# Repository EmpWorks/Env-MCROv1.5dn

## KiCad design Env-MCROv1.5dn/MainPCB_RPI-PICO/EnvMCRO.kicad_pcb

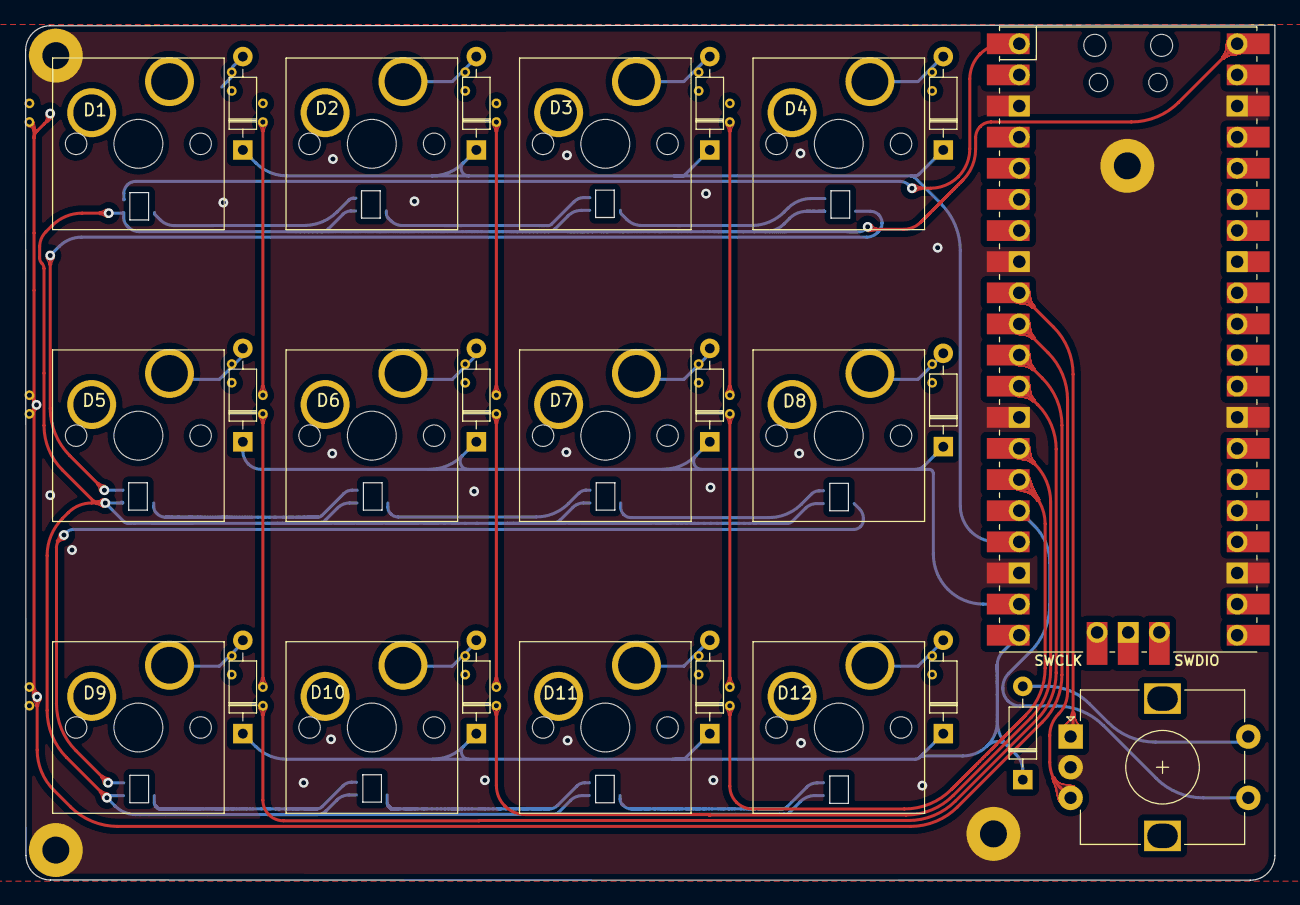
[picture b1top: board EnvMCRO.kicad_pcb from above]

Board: 2 copper layers, 101.9 x 69.8 mm, 43 parts (0 on the bottom side), 37 nets.

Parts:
D1, D2, D3, D4, D5, D6, D7, D8, D9, D10, D11, D12: WS2812B; LED_WS2812B-5050_PLCC4_5.0x5.0mm_P3.2mm
D_0, D_1, D_2, D_3, D_4, D_5, D_6, D_7, D_8, D_9, D_10, D_11, D_14: D; D_DO-35_SOD27_P7.62mm_Horizontal
H1, H2, H3, H4: MountingHole; MountingHole_2.2mm_M2_Pad
K_0, K_1, K_2, K_3, K_4, K_5, K_6, K_7, K_8, K_9, K_10, K_11: KEYSW; MXOnly-1U-Hotswap-Antishear
SW1: Rotary_Encoder_Switch; RotaryEncoder_Alps_EC12E-Switch_Vertical_H20mm
U1: Pico; RPi_Pico_SMD_TH

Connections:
GND: D1.3 (VSS), D2.3 (VSS), D3.3 (VSS), D4.3 (VSS), D5.3 (VSS), D6.3 (VSS), D7.3 (VSS), D8.3 (VSS), D9.3 (VSS), D10.3 (VSS), D11.3 (VSS), D12.3 (VSS), H1.1, H2.1, H3.1, H4.1, SW1.C, U1.3 (GND), U1.8 (GND), U1.13 (GND), U1.18 (GND), U1.23 (GND), U1.28 (GND), U1.38 (GND)
LEDDINPIN: D1.4 (DIN), U1.1 (GPIO0)
unnamed: D1.2 (DOUT), D2.4 (DIN)
unnamed: D2.2 (DOUT), D3.4 (DIN)
unnamed: D3.2 (DOUT), D4.4 (DIN)
unnamed: D4.2 (DOUT), D5.4 (DIN)
unnamed: D5.2 (DOUT), D6.4 (DIN)
unnamed: D6.2 (DOUT), D7.4 (DIN)
unnamed: D7.2 (DOUT), D8.4 (DIN)
unnamed: D8.2 (DOUT), D9.4 (DIN)
unnamed: D10.2 (DOUT), D11.4 (DIN)
unnamed: D9.2 (DOUT), D10.4 (DIN)
unnamed: D11.2 (DOUT), D12.4 (DIN)
unnamed: D_0.2 (A), K_0.2 (ROW)
unnamed: D_1.2 (A), K_1.2 (ROW)
unnamed: D_2.2 (A), K_2.2 (ROW)
unnamed: D_3.2 (A), K_3.2 (ROW)
unnamed: D_4.2 (A), K_4.2 (ROW)
unnamed: D_5.2 (A), K_5.2 (ROW)
unnamed: D_6.2 (A), K_6.2 (ROW)
unnamed: D_7.2 (A), K_7.2 (ROW)
unnamed: D_8.2 (A), K_8.2 (ROW)
unnamed: D_9.2 (A), K_9.2 (ROW)
unnamed: D_10.2 (A), K_10.2 (ROW)
unnamed: D_11.2 (A), K_11.2 (ROW)
unnamed: D_14.2 (A), SW1.S1
ROTA: SW1.B, U1.10 (GPIO7)
ROTB: SW1.A, U1.9 (GPIO6)
VBUS: D1.1 (VDD), D2.1 (VDD), D3.1 (VDD), D4.1 (VDD), D5.1 (VDD), D6.1 (VDD), D7.1 (VDD), D8.1 (VDD), D9.1 (VDD), D10.1 (VDD), D11.1 (VDD), D12.1 (VDD), U1.40 (VBUS)
col0: K_0.1 (COL), K_4.1 (COL), K_8.1 (COL), U1.11 (GPIO8)
col1: K_1.1 (COL), K_5.1 (COL), K_9.1 (COL), U1.12 (GPIO9)
col2: K_2.1 (COL), K_6.1 (COL), K_10.1 (COL), U1.14 (GPIO10)
col3: K_3.1 (COL), K_7.1 (COL), K_11.1 (COL), U1.15 (GPIO11)
col4: SW1.S2, U1.16 (GPIO12)
row0: D_0.1 (K), D_1.1 (K), D_2.1 (K), D_3.1 (K), U1.17 (GPIO13)
row1: D_4.1 (K), D_5.1 (K), D_6.1 (K), D_7.1 (K), U1.19 (GPIO14)
row2: D_8.1 (K), D_9.1 (K), D_10.1 (K), D_11.1 (K), D_14.1 (K), U1.20 (GPIO15)

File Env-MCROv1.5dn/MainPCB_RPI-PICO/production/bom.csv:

Designator,Footprint,Quantity,Value,LCSC Part #
K_4,MXOnly-1U-Hotswap-Antishear,1,KEYSW,
D_6,D_DO-35_SOD27_P7.62mm_Horizontal,1,D,
D_0,D_DO-35_SOD27_P7.62mm_Horizontal,1,D,
K_0,MXOnly-1U-Hotswap-Antishear,1,KEYSW,
D_7,D_DO-35_SOD27_P7.62mm_Horizontal,1,D,
H1,MountingHole_2.2mm_M2_Pad,1,MountingHole,
H4,MountingHole_2.2mm_M2_Pad,1,MountingHole,
H3,MountingHole_2.2mm_M2_Pad,1,MountingHole,
H2,MountingHole_2.2mm_M2_Pad,1,MountingHole,
U1,RPi_Pico_SMD_TH,1,Pico,
D1,LED_WS2812B-5050_PLCC4_5.0x5.0mm_P3.2mm,1,WS2812B,
D2,LED_WS2812B-5050_PLCC4_5.0x5.0mm_P3.2mm,1,WS2812B,
D3,LED_WS2812B-5050_PLCC4_5.0x5.0mm_P3.2mm,1,WS2812B,
D4,LED_WS2812B-5050_PLCC4_5.0x5.0mm_P3.2mm,1,WS2812B,
D5,LED_WS2812B-5050_PLCC4_5.0x5.0mm_P3.2mm,1,WS2812B,
D6,LED_WS2812B-5050_PLCC4_5.0x5.0mm_P3.2mm,1,WS2812B,
D7,LED_WS2812B-5050_PLCC4_5.0x5.0mm_P3.2mm,1,WS2812B,
D8,LED_WS2812B-5050_PLCC4_5.0x5.0mm_P3.2mm,1,WS2812B,
D9,LED_WS2812B-5050_PLCC4_5.0x5.0mm_P3.2mm,1,WS2812B,
D10,LED_WS2812B-5050_PLCC4_5.0x5.0mm_P3.2mm,1,WS2812B,
D11,LED_WS2812B-5050_PLCC4_5.0x5.0mm_P3.2mm,1,WS2812B,
D12,LED_WS2812B-5050_PLCC4_5.0x5.0mm_P3.2mm,1,WS2812B,
SW1,RotaryEncoder_Alps_EC12E-Switch_Vertical_H20mm,1,Rotary_Encoder_Switch,
D_14,D_DO-35_SOD27_P7.62mm_Horizontal,1,D,
K_1,MXOnly-1U-Hotswap-Antishear,1,KEYSW,
D_3,D_DO-35_SOD27_P7.62mm_Horizontal,1,D,
D_10,D_DO-35_SOD27_P7.62mm_Horizontal,1,D,
K_5,MXOnly-1U-Hotswap-Antishear,1,KEYSW,
D_4,D_DO-35_SOD27_P7.62mm_Horizontal,1,D,
D_8,D_DO-35_SOD27_P7.62mm_Horizontal,1,D,
D_5,D_DO-35_SOD27_P7.62mm_Horizontal,1,D,
K_9,MXOnly-1U-Hotswap-Antishear,1,KEYSW,
K_8,MXOnly-1U-Hotswap-Antishear,1,KEYSW,
D_2,D_DO-35_SOD27_P7.62mm_Horizontal,1,D,
D_1,D_DO-35_SOD27_P7.62mm_Horizontal,1,D,
K_11,MXOnly-1U-Hotswap-Antishear,1,KEYSW,
K_6,MXOnly-1U-Hotswap-Antishear,1,KEYSW,
K_10,MXOnly-1U-Hotswap-Antishear,1,KEYSW,
K_3,MXOnly-1U-Hotswap-Antishear,1,KEYSW,
D_9,D_DO-35_SOD27_P7.62mm_Horizontal,1,D,
K_2,MXOnly-1U-Hotswap-Antishear,1,KEYSW,
D_11,D_DO-35_SOD27_P7.62mm_Horizontal,1,D,
K_7,MXOnly-1U-Hotswap-Antishear,1,KEYSW,
